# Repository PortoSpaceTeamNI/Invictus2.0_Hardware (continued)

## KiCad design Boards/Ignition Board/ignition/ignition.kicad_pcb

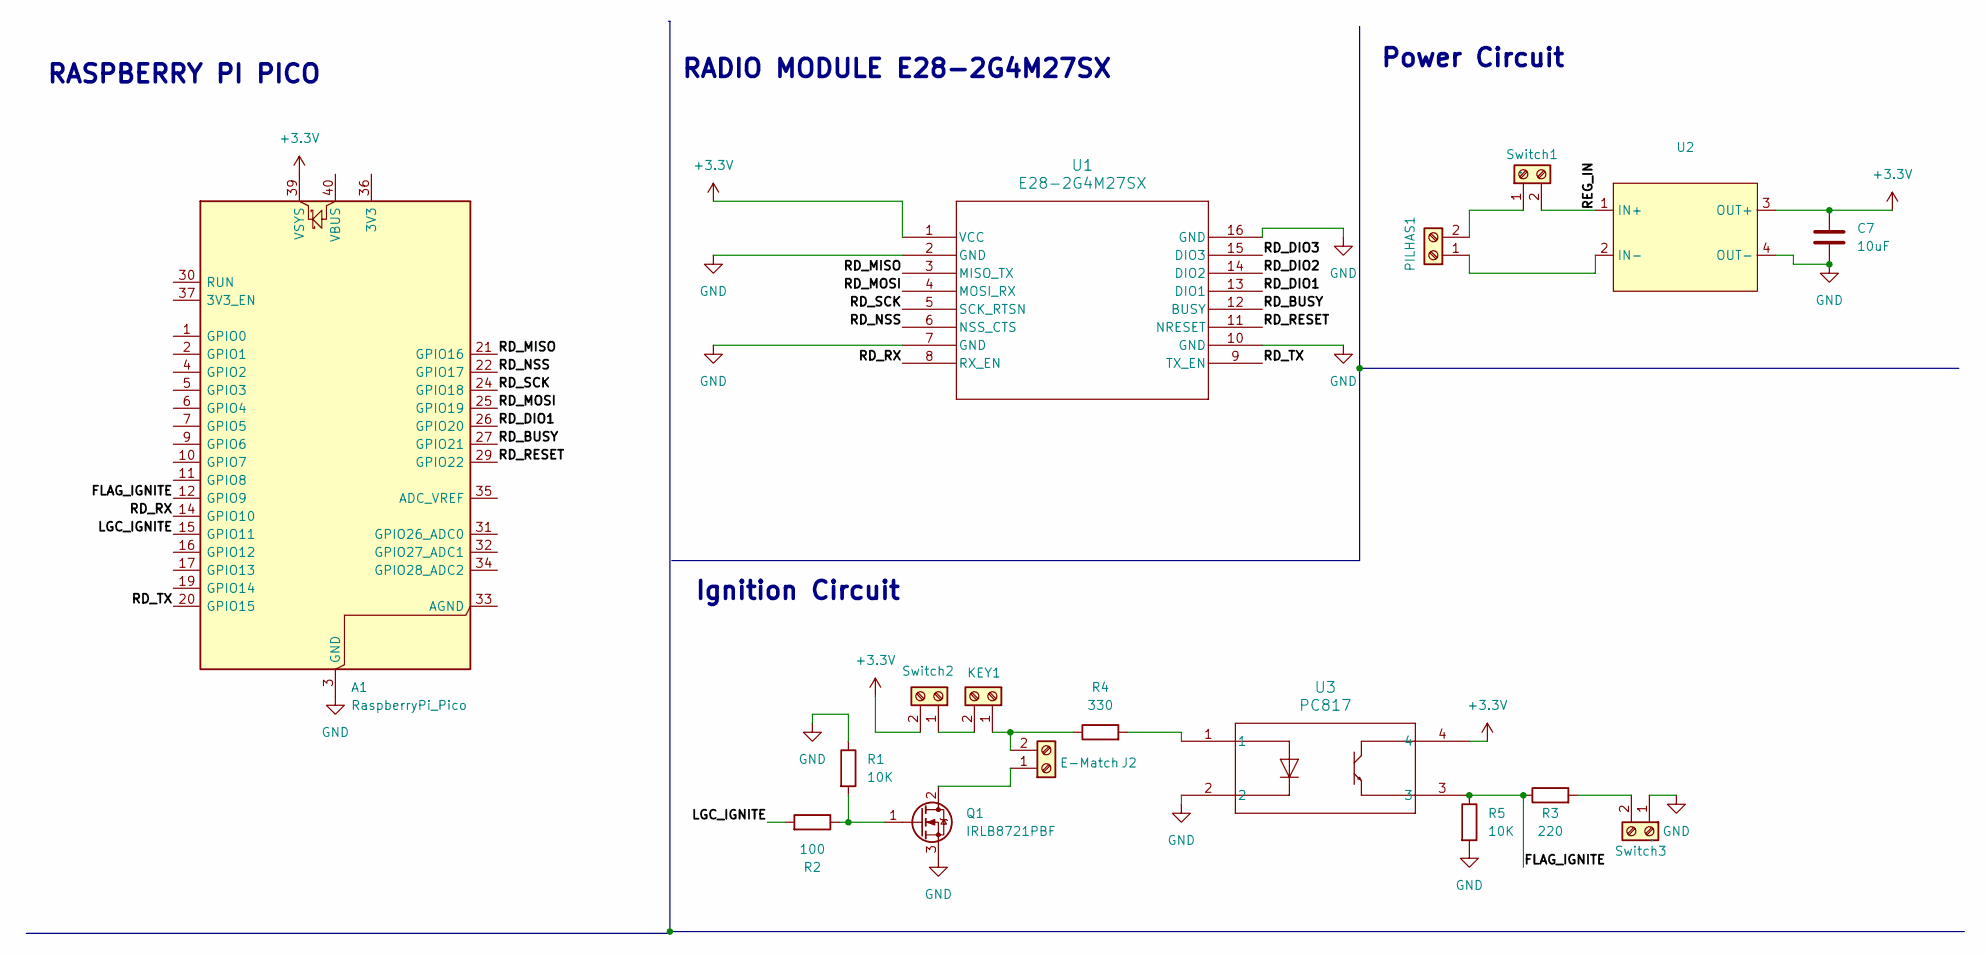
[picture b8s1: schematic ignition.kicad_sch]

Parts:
A1: RaspberryPi_Pico; RaspberryPi_Pico_Common_Unspecified
C7: 10uF; C_0402_1005Metric
J2: E-Match; TerminalBlock_Xinya_XY308-2.54-2P_1x02_P2.54mm_Horizontal
KEY1: Screw_Terminal_01x02; TerminalBlock_Xinya_XY308-2.54-2P_1x02_P2.54mm_Horizontal
PILHAS1: Screw_Terminal_01x02; TerminalBlock_Xinya_XY308-2.54-2P_1x02_P2.54mm_Horizontal
Q1: IRLB8721PBF; TO-220-3_Vertical
R1, R5: 10K; R_0402_1005Metric
R2: 100; R_0402_1005Metric
R3: 220; R_0402_1005Metric
R4: 330; R_0402_1005Metric
Switch1, Switch3: .; TerminalBlock_Xinya_XY308-2.54-2P_1x02_P2.54mm_Horizontal
Switch2: Screw_Terminal_01x02; TerminalBlock_Xinya_XY308-2.54-2P_1x02_P2.54mm_Horizontal
U1: E28-2G4M27SX; Radio_Module_PST
U2: DCDC_Module
U3: PC817; PC817X_SHP

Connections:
+3.3V: A1.39 (VSYS), C7.1, Switch2.2, U1.1 (VCC), U2.3 (OUT+), U3.4
/FLAG_IGNITE: A1.12 (GPIO9), R3.1, R5.1, U3.3
/LGC_IGNITE: A1.15 (GPIO11), R2.2
/RD_BUSY: A1.27 (GPIO21), U1.12 (BUSY)
/RD_DIO1: A1.26 (GPIO20), U1.13 (DIO1)
/RD_DIO2: U1.14 (DIO2)
/RD_DIO3: U1.15 (DIO3)
/RD_MISO: A1.21 (GPIO16), U1.3 (MISO_TX)
/RD_MOSI: A1.25 (GPIO19), U1.4 (MOSI_RX)
/RD_NSS: A1.22 (GPIO17), U1.6 (NSS_CTS)
/RD_RESET: A1.29 (GPIO22), U1.11 (NRESET)
/RD_RX: A1.14 (GPIO10), U1.8 (RX_EN)
/RD_SCK: A1.24 (GPIO18), U1.5 (SCK_RTSN)
/RD_TX: A1.20 (GPIO15), U1.9 (TX_EN)
/REG_IN: Switch1.2, U2.1 (IN+)
GND: A1.3 (GND), A1.8 (GND), A1.13 (GND), A1.18 (GND), A1.23 (GND), A1.28 (GND), A1.38 (GND), C7.2, Q1.3 (S), R1.1, R5.2, Switch3.1, U1.2 (GND), U1.7 (GND), U1.10 (GND), U1.16 (GND), U2.4 (OUT-), U3.2
unnamed: J2.1, Q1.2 (D)
unnamed: J2.2, KEY1.1, R4.1
unnamed: KEY1.2, Switch2.1
unnamed: PILHAS1.1, U2.2 (IN-)
unnamed: PILHAS1.2, Switch1.1
unnamed: Q1.1 (G), R1.2, R2.1
unnamed: R4.2, U3.1
unnamed: R3.2, Switch3.2

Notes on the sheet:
Ignition Circuit
Power Circuit
RADIO MODULE E28-2G4M27SX
RASPBERRY PI PICO

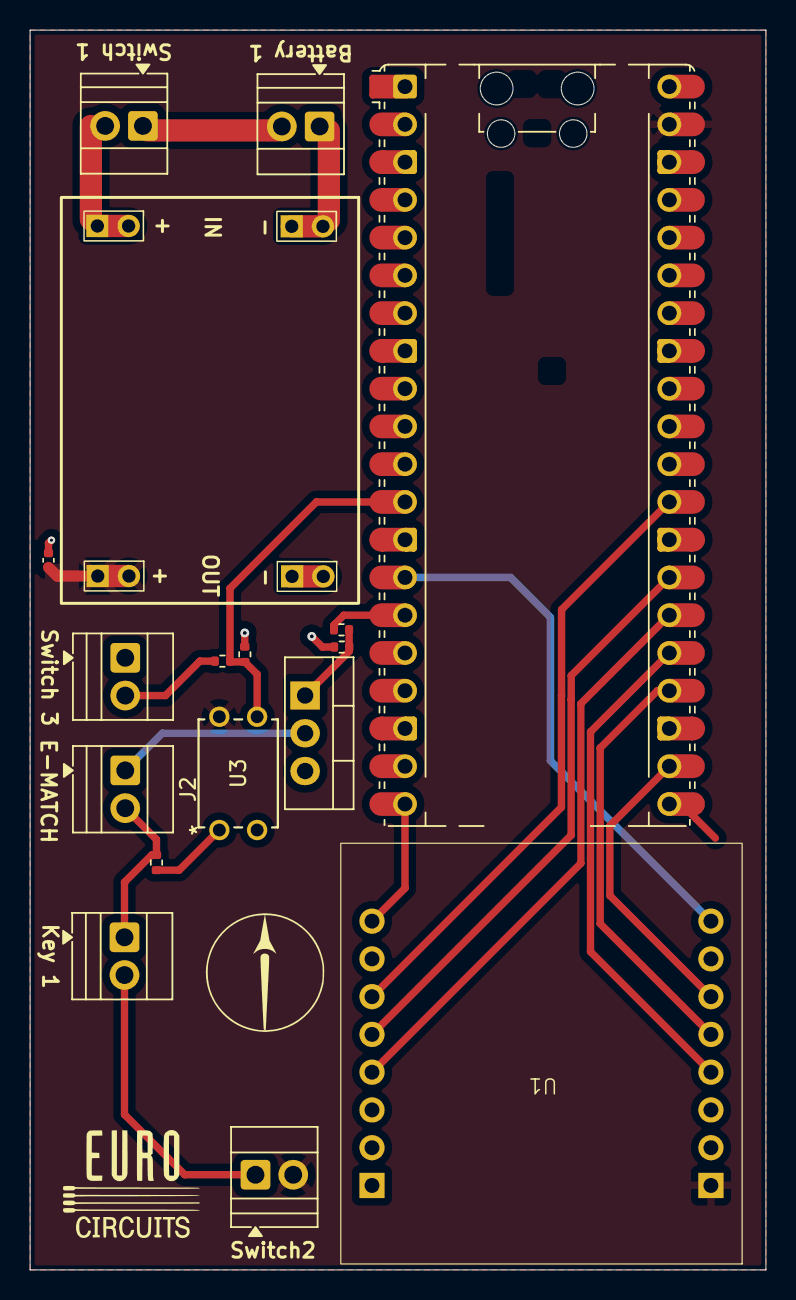
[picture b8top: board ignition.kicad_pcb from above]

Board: 2 copper layers, 49.5 x 83.4 mm, 17 parts (0 on the bottom side), 22 nets.

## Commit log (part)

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2024-12-28 Inclusão do projeto RP2040 Standard Design
2024-12-28 organização do repo
2024-12-29 Footprint teste
2024-12-29 c12 footprint
2024-12-29 To do list update: Comms board
    Corrigir erros do ERC e teste de sincronização do repo
2024-12-29 Update .gitignore
    exclude prl files
2024-12-29 teste do gitignore modificado
2024-12-29 Adição de Connectors
    Connector "CONN Female Header 22022065" adicionado à library
    Connectors do UART, 5V e GND adicionados à OBC
2024-12-29 parte 2
    é isso
2024-12-30 Preparação do RP2040 para PCB Design
    Foram corrigidos todos os ERC errors e warnings. Foram feitas alterações
    aos necessários simbolos, e foi adicionado um botão na biblioteca de
    simbolos
2024-12-30 Correção de erros ERC no OBC e correção de simbolos usados
2024-12-30 Correção de erros ERC na Communication Board
    Foram corrigidos todos os erros e avisos ERC na Communication Board.
    Foram feitas alterações aos ficheiros de alguns símbolos e adicionou-se
    um Schottky Diode de proteção
2024-12-31 atualização simbolos thermocouples
2024-12-31 correção de alguns erros ERC CANha
2025-01-01 Correção do últimos erros ERC e adição do sensor de temperatura
    Tbm revi a linha do ADC, adicionei novos simbolos incluindo um NMOS
    MOSFET e um Schottky
2025-01-03 pequenas alterações, implementação do sensor de temperatura na placa de comunicações
2025-01-09 Atualização footprints
    Footprints das resistencias, condensadores e indutores + Ferrite
2025-01-09 USB-C update
2025-01-10 Atualizações footprints
    Adicionei a Resistência de 27 ohms que faltava na biblioteca Symbols Lib;
    Atualizei as footprints do OBC menos a componente J6;
2025-01-10 COMS
    Acho que já está tudo de footprints que tinha que fazer na Communication Board
2025-01-11 Atualização footprint RP2040
2025-01-11 Atualização CANha
2025-01-11 Connectors Para Comunicação RS e ADC
    Connetctors de 2, 3 e 5 entradas utilizados no RP2040 Standard, OBC, CANha e Communication adicionados à pasta de Símbolos
2025-01-11 Mudança de nome das footprints
2025-01-11 pequenas correções em algumas resistências e bugfix do simobolo do Barometro
2025-01-12 bugfix do pull request merge
2025-01-23 changes in RP2040 design
    GPIO25 LED is now part of RP2040 Standard
2025-01-25 Reorganização da biblioteca de simbolos por categorias
    A SymbolsLib foi atualizada para estar por categorias
2025-01-25 Repo Refactor and new systems update
2025-01-25 Inicio de integração do RF FEM nas placas de comunicação
2025-01-26 Led driver circuit correction & RF FEM implementation
2025-01-27 Sockets Pico_Conn
    Adição à Library e ao RP2040 S de Sockets iguais às placas de Pico.
2025-01-27 ADS1115 implementation
2025-01-27 Male CONN adicionado e OBC atualizado
    - Connector macho que liga a R COMMS ao OBC adicionado à biblioteca
    - OBC com as footprints atualizadas
2025-01-27 Adicionado a conexão ao R COMMS
    R COMMS
2025-01-28 OBC
    Contactos Pico adicionados à OBC
2025-01-28 Mais Sockets Pico
    TVCS Top, Bottom and Fill and G&F COMMS
2025-01-28 XT30 to XT60
    Connectores atualizados em toda as TVCS
2025-01-28 RP2040 FOOTPRINTS
2025-01-28 Footprints (RP2040 Corrigido e OBC)
2025-01-29 git ignore edit
2025-01-30 DC DC Design
2025-01-30 Mudanças nas Schematics
    - Capacitor-0805 adicionado à library
    - Nomes de Passive Components atualizados na library
    - Atualizado as footprint dos RP2040 S, OBC, R COMMS
2025-01-31 Final DCDC design and update part1 COMM board
2025-01-31 Library
    Vários Footprints de Capacitors e Inductors
2025-01-31 Update R Comms board
2025-01-31 Tu viste o q eu fiz
2025-01-31 TVCS PERFECT
    ou quase
2025-01-31 Communication boards update
2025-02-01 System update
2025-02-03 integração inicial da USB-C PD controller
2025-02-04 USB-C PD update and schematic corrections
2025-02-06 Sensor corrente v1
2025-02-10 Current sensor update implementation and 8.4V DC.DC implementation
2025-02-11 TVCS rework
2025-02-11 TVCS pinout rework
2025-02-11 OBC, DC.DC Converter atualizado
2025-02-12 I2C translator symbol fix and TVCS final touches
2025-02-12 TVCS final Design
2025-02-13 Alterações RP2040 P
2025-02-15 Atualiza labels no OBC.kicad_sch
2025-02-16 RP2040 S PCB (Part #1)
    Diversos crimes de guerra contra as pcbs foram cometidos com esta alteração. Ao dar merge está a compactuar com os ditos crimes e terá de confrontar as autoridades.
2025-02-16 Part #2
2025-02-16 Atualização 2 RP2040 P
2025-02-20 atualização 3
2025-02-20 Atualização 4
2025-02-21 TVCS final Update. Finished Schematic
2025-02-22 Communication System final Schematic Update
2025-02-22 RP2040 PCB (Part 3)
2025-02-23 Esqueci-me da RP2040 S
2025-02-23 Símbolo do potenciómetro
2025-02-23 Adiciona novo componente de medição de humidade
2025-02-23 Development board update
2025-02-23 lib humidity update
2025-02-27 TVCS Dev
    Copiei as footprints todas de uma vez
2025-02-27 Payload Project
2025-03-01 RP2040 S (Part 4)
    Teste de algumas aprendizagens dos últimos tempos e inserindo as regras da EUROCIRCUITS ("BGA Component: Poolable Options")
2025-03-02 organizar a PCB
2025-03-03 mudei cores
2025-03-03 Mudança de cores
2025-03-04 teste
2025-03-04 RP2040 S (Part 5)
2025-03-04 cores na Dev
2025-03-07 3D Symbols Update and R Comms PCB layout (1)
2025-03-08 R COMMS layout placement
2025-03-09 3D models update
2025-03-09 Layout PCB
2025-03-09 commit to fix merge (1)
2025-03-10 OBC layout update
2025-03-10 RP2040 S (Part 6)
    tá bom pra hj
2025-03-10 RP2040 S review
2025-03-20 continuação
2025-03-20 Reset PCB Payload
2025-03-23 full update on RCOMMS layout
2025-03-25 RP2040 (tá quase)
2025-03-25 RP2040S ()
    acho q tá feito
2025-03-25 RP2040S (update)
    mudar resistências de tamanho e ajustes que vieram com isso
2025-04-06 TVCS refactor
    Muitas alterações e correções na placa TVCSO:
    Novo ADC, filtros passa baixo, novo RS transceiver, reformulação de
    conexões
2025-04-07 TVCS fixes and required additions
2025-04-08 small pinout update
2025-04-08 Gnd update
2025-04-09 Add files via upload
    upload to windows
2025-04-11 added a driver for the led in the adc
2025-04-17 Pocket Stat Lib update
2025-04-17 Pocket Stat Schematic Notation Update
2025-04-17 pocketstat power update
2025-04-18 Navigator update
2025-04-18 OBC a Navigator Updates
2025-04-18 temp sensor filter
2025-04-19 layout initialization
2025-04-19 ESD diodes and pinout update
2025-04-19 ESD diode update
2025-04-19 small esd diode update
2025-04-19 partial rounting done
2025-04-21 OBC & Navigator updates
2025-04-22 first version of the routing, missing DRC rulecheck and silkscreen mapping
2025-04-24 Update PCB Payload
    Acabei o routing do ground e coloquei as camadas de GND;
2025-04-25 update RP DEV
2025-04-30 minor changes
2025-05-02 Nav & OBC update
2025-05-07 slikcreen and DRC corrections navigator
2025-05-08 OBC routing
2025-05-08 Update PCB Payload
    Routing PCB para analise
2025-05-12 Finished OBC
2025-05-13 Silkcreen and Logos
2025-05-17 PocketSat
2025-05-17 Footprint Edit
2025-05-17 PocketSat Finished
2025-05-17 project rename
2025-05-17 OBC ground updates
2025-05-17 PocketStat Ground Planes Update
2025-05-31 OBC DFM corrections
2025-05-31 OBC DFM adjustments
2025-05-31 Final adjustments
2025-06-04 obc schematic
2025-06-06 OBC final BOM and Fabfiles
2025-07-02 Hydra Breakout
2025-07-05 Design da Hydra Breakout (Part 1)
    Inclui algumas adições à biblioteca.
2025-07-05 Mouse Bites
2025-07-07 Design da Hydra Breakout (Part 2)
2025-07-09 Adicionei um driver novo de leds e outras correçoes
    Adicionei um novo driver de leds substitui pelo velho e corrigimos mais
    erros de DRC
2025-07-09 Correção DFM JLC
    Modifiquei a PCB para passar em todos os criterios da JLC DFM
2025-07-09 mudanca na solder expansion
    mudei a solder expansion de alguma footprints do pocketsat para se
    encaixarem com as regras da DFM da JLCPCB
2025-07-12 Esquematica Elytra
    Fiz parte da esquematica da Elytra
2025-07-12 Elytra Schematic & Symbol Update
2025-07-12 Symbols Update
2025-07-12 PocketSat small fixes
2025-07-12 circuito
    Circuito
2025-07-15 HYDRA Update
2025-07-17 elytra added to navigator
2025-07-17 drc and new components added
2025-07-17 Inicio da PCB Elytra
    Tive um problema com algumas footprints, tive de recomecar a pcb
2025-07-17 OBC Full layout refactor, HYDRA Schematics UPDATE
2025-07-18 Design da Hydra Breakout (Part 3)
2025-07-19 elytra added and full routing done
2025-07-20 Rounting and DRC done
2025-07-20 OBC Updates
2025-07-20 Navigator PCB outline update
2025-07-20 final touches
2025-07-23 Design da Hydra Breakout (Part 4)
2025-07-24 OBC Final Update - DFM corrections
2025-07-24 Navigator silkcreen
2025-07-24 Navigator Silkscreen Changes
2025-07-26 Navigator Final Update - DFM corrections
2025-07-26 OBC - footprint updates
2025-07-27 Continuaçao desenvolvimento Elytra
    Continuacao desenvolvimento Elytra
2025-07-27 mais updates pcb elyra
2025-07-28 update pcb elytra
    update a pcb elytra + modificacao footprint conversor
2025-07-30 Design da Hydra Breakout (Part 5)
2025-07-30 updated the ADC routing in schematic
2025-07-31 Hydra
2025-08-02 OBC, Nav, PocketSat review - SPI and I2C mistakes corrected
2025-08-02 load cell udpates
2025-08-02 Mudancas PCB Elytra
    Mudancas PCB Elytra
2025-08-02 mudancas pcb elytra
2025-08-03 major changes on the HYDRA schematic including valve actuation and adc changes
2025-08-04 Reordered the DC DC schematic
2025-08-07 Full HYDRA UPDATE
2025-08-07 IO connectors
2025-08-08 ADC sense squematic done
2025-08-08 bessels filter - anti aliasing
2025-08-08 Elytra
2025-08-10 corrected some ERC and changed the Connector
2025-08-10 ELYTRA FULL UPDATE
2025-08-10 Started routing for elytra
2025-08-10 Adiciona Footprint Thermocouple
    Adiciona Footprint ThermoPCBConnector a Contacts and Switches
2025-08-10 HYDRA Schematic Update Final Touches
2025-08-10 HYDRA schematic pinout update pt1
2025-08-12 Elytra Update
2025-08-13 Acabamentos da PCB Elytra
    Elytra Finalizada e pronta para ser enviada
2025-08-15 HYDRA schematic update, ELYTRA FULL REWORK
2025-08-16 DFM checks, Avionics Updates
2025-08-16 Elytra, OBC, Nav Eurocircuits DFM - production checks
2025-08-21 elytra step update
2025-09-01 HYDRA Update - footprints and schematics
2025-09-02 Electrical Harness PCB
    Electrical Harness PCB
2025-09-05 HYDRA placemenent
2025-09-09 HYDRA full design for manufacturing
2025-09-29 PCB CALHA
    PCB CALHA
2025-12-02 PCB's Loadcells
    Continuei a trabalhar na esquematica das pcbs das loadcells
2025-12-06 PCB Loadcell
    Acabei a PCB Loadcell ( Disposto a mudanças). Vai ser reviewed pelo Alexandre.
2025-12-08 PCB Loadcells Acabada
    Acabei o design das pcbs das loadcells, so falta colocar os logos e buracos m3.
2025-12-09 PCB Loadcells
    Agora sim acho que ta acabado
2025-12-10 PCB LOADCELLS
    PCB LOADCELLS
2025-12-10 PCB Lift Final
    PCB Lift Final
2025-12-14 LIFT PCB
    LIFT PCB
2025-12-14 PCB LIFT
    PCB LIFT
2025-12-17 LIFT PCB
    LIFT PCB FINAL
2026-01-12 PCB LIFT CAN BUS
    adicionei um controlador de can para futuras implementaçoes
2026-01-12 PCB LIFT CAN
    CAN BUS ADDED
2026-01-30 added stm32 symbol and footprint
2026-02-02 added radio module
2026-02-02 edge cuts
2026-02-03 Main components placed
2026-02-03 LIFT
    lift
2026-02-03 progress
2026-02-10 Sparky PCB Ignition
    Sparky PCB Ignition
2026-02-10 MissionControl
    Controlar a missão ahh board
2026-02-14 Algumas mudancas nas PCBs
    Algumas mudancas nas PCBs
2026-02-17 Atualização
2026-02-19 Cortex Update
2026-02-22 Ignition Changes
2026-02-23 resolvido :)
2026-03-04 PCBs acabadas e modulo de radio feito
2026-03-12 Cortex FIM
2026-03-12 cortex
2026-03-19 STM32G4 Breakout Board
2026-03-31 Remove Before Flight
2026-04-06 GNC_Board
2026-04-10 gnc_board_th
2026-04-10 blah
2026-04-13 PMU (New Elytra)
    Primeiras edições e To Do List
2026-04-14 Algumas mudancas no cortex
2026-04-16 PMU continuacíon
    coisas
2026-04-18 PMU quase
    Umas adições à lib e a PMU quase finalizada
2026-04-22 Updated cortex_smd
2026-04-23 PMU
    Adição de várias footprints e pequenos ajustes na schematic
2026-04-25 PMU BROW BROW
2026-04-25 PMU layout
    Full layout
2026-04-27 gerbers
2026-04-29 PMU banger
2026-05-13 PMU
    adição de buffers
2026-05-17 PMU
    Troca de DC DC e adição de algum labeling que faltava
